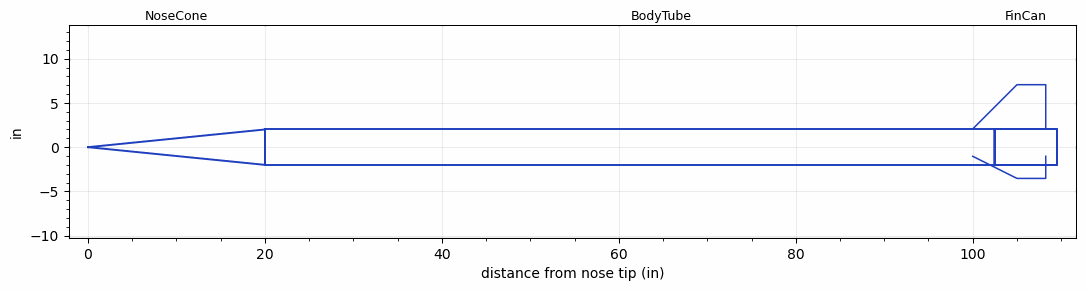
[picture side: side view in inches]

<RASAeroDocument>
 <FileVersion>2</FileVersion>
 <RocketDesign>
  <NoseCone>
   <Length>20</Length>
   <Diameter>4</Diameter>
   <Shape>Conical</Shape>
   <BluntRadius>0.031</BluntRadius>
   <Location>0</Location>
  </NoseCone>
  <BodyTube>
   <Length>89.5</Length>
   <Diameter>4</Diameter>
   <Location>20</Location>
  </BodyTube>
  <FinCan>
   <Length>7</Length>
   <Diameter>4.125</Diameter>
   <InsideDiameter>4</InsideDiameter>
   <RailGuideDiameter>0.375</RailGuideDiameter>
   <RailGuideHeight>0.5</RailGuideHeight>
   <Location>109.5</Location>
   <ShoulderLength>0.05</ShoulderLength>
   <Offset>-7</Offset>
   <Fin>
    <Count>3</Count>
    <Chord>8.25</Chord>
    <Span>5</Span>
    <SweepDistance>5</SweepDistance>
    <TipChord>3.25</TipChord>
    <Thickness>0.125</Thickness>
    <Location>9.5</Location>
    <AirfoilSection>Rounded</AirfoilSection>
    <FX1>0.125</FX1>
    <FX3>0.125</FX3>
   </Fin>
  </FinCan>
  <Surface>Smooth (Zero Roughness)</Surface>
  <ModifiedBarrowman>False</ModifiedBarrowman>
  <Turbulence>False</Turbulence>
  <SustainerNozzle>1.625</SustainerNozzle>
  <UseBooster1>False</UseBooster1>
  <UseBooster2>False</UseBooster2>
  <Comments>Torrent
Ray Kinsel
Rocket launched 2 May 2008
ALX1 file rocket data provided by Ray Kinsel

Barometric Altimeter
Altitude = 12807 ft

RASAero II Prediction = 13717 ft
Error = 7.11%
</Comments>
 </RocketDesign>
 <LaunchSite>
  <Altitude>2400</Altitude>
  <Pressure>29.85</Pressure>
  <RodAngle>0</RodAngle>
  <RodLength>10</RodLength>
  <Temperature>80</Temperature>
  <WindSpeed>10</WindSpeed>
 </LaunchSite>
 <Recovery>
  <Altitude1>1000</Altitude1>
  <Altitude2>1000</Altitude2>
  <DeviceType1>Parachute</DeviceType1>
  <DeviceType2>None</DeviceType2>
  <Event1>True</Event1>
  <Event2>False</Event2>
  <Size1>108</Size1>
  <Size2>1</Size2>
  <EventType1>Apogee</EventType1>
  <EventType2>None</EventType2>
  <CD1>1.33</CD1>
  <CD2>1.33</CD2>
 </Recovery>
 <SimulationList>
  <Simulation>
   <SustainerEngine>M1850GG  (AMW)</SustainerEngine>
   <SustainerLaunchWt>29.13</SustainerLaunchWt>
   <SustainerNozzleDiameter>1.625</SustainerNozzleDiameter>
   <SustainerCG>66.5</SustainerCG>
   <SustainerIgnitionDelay>0</SustainerIgnitionDelay>
   <Booster1SeparationDelay>0</Booster1SeparationDelay>
   <Booster1IgnitionDelay>0</Booster1IgnitionDelay>
   <IncludeBooster1>False</IncludeBooster1>
   <Booster2Delay>0</Booster2Delay>
   <IncludeBooster2>False</IncludeBooster2>
   <TimetoApogee>27.13053</TimetoApogee>
   <MaxAltitude>13716.88</MaxAltitude>
   <MaxVelocity>1404.335</MaxVelocity>
  </Simulation>
 </SimulationList>
</RASAeroDocument>
